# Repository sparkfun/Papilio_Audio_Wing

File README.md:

Papilio Audio Wing
==================
[  
*Papilio Audio Wing (WIG-11568)*](https://www.sparkfun.com/products/11568)

This board allows you to quickly add 2 stereo channels to your Papilio FPGA board. 

Repository Contents
-------------------
* **/Hardware** - All Eagle design files (.brd, .sch)
* **/Production** - Test bed files and production panel files

License Information
-------------------
The hardware is released under [Creative Commons Share-alike 3.0](http://creativecommons.org/licenses/by-sa/3.0/).

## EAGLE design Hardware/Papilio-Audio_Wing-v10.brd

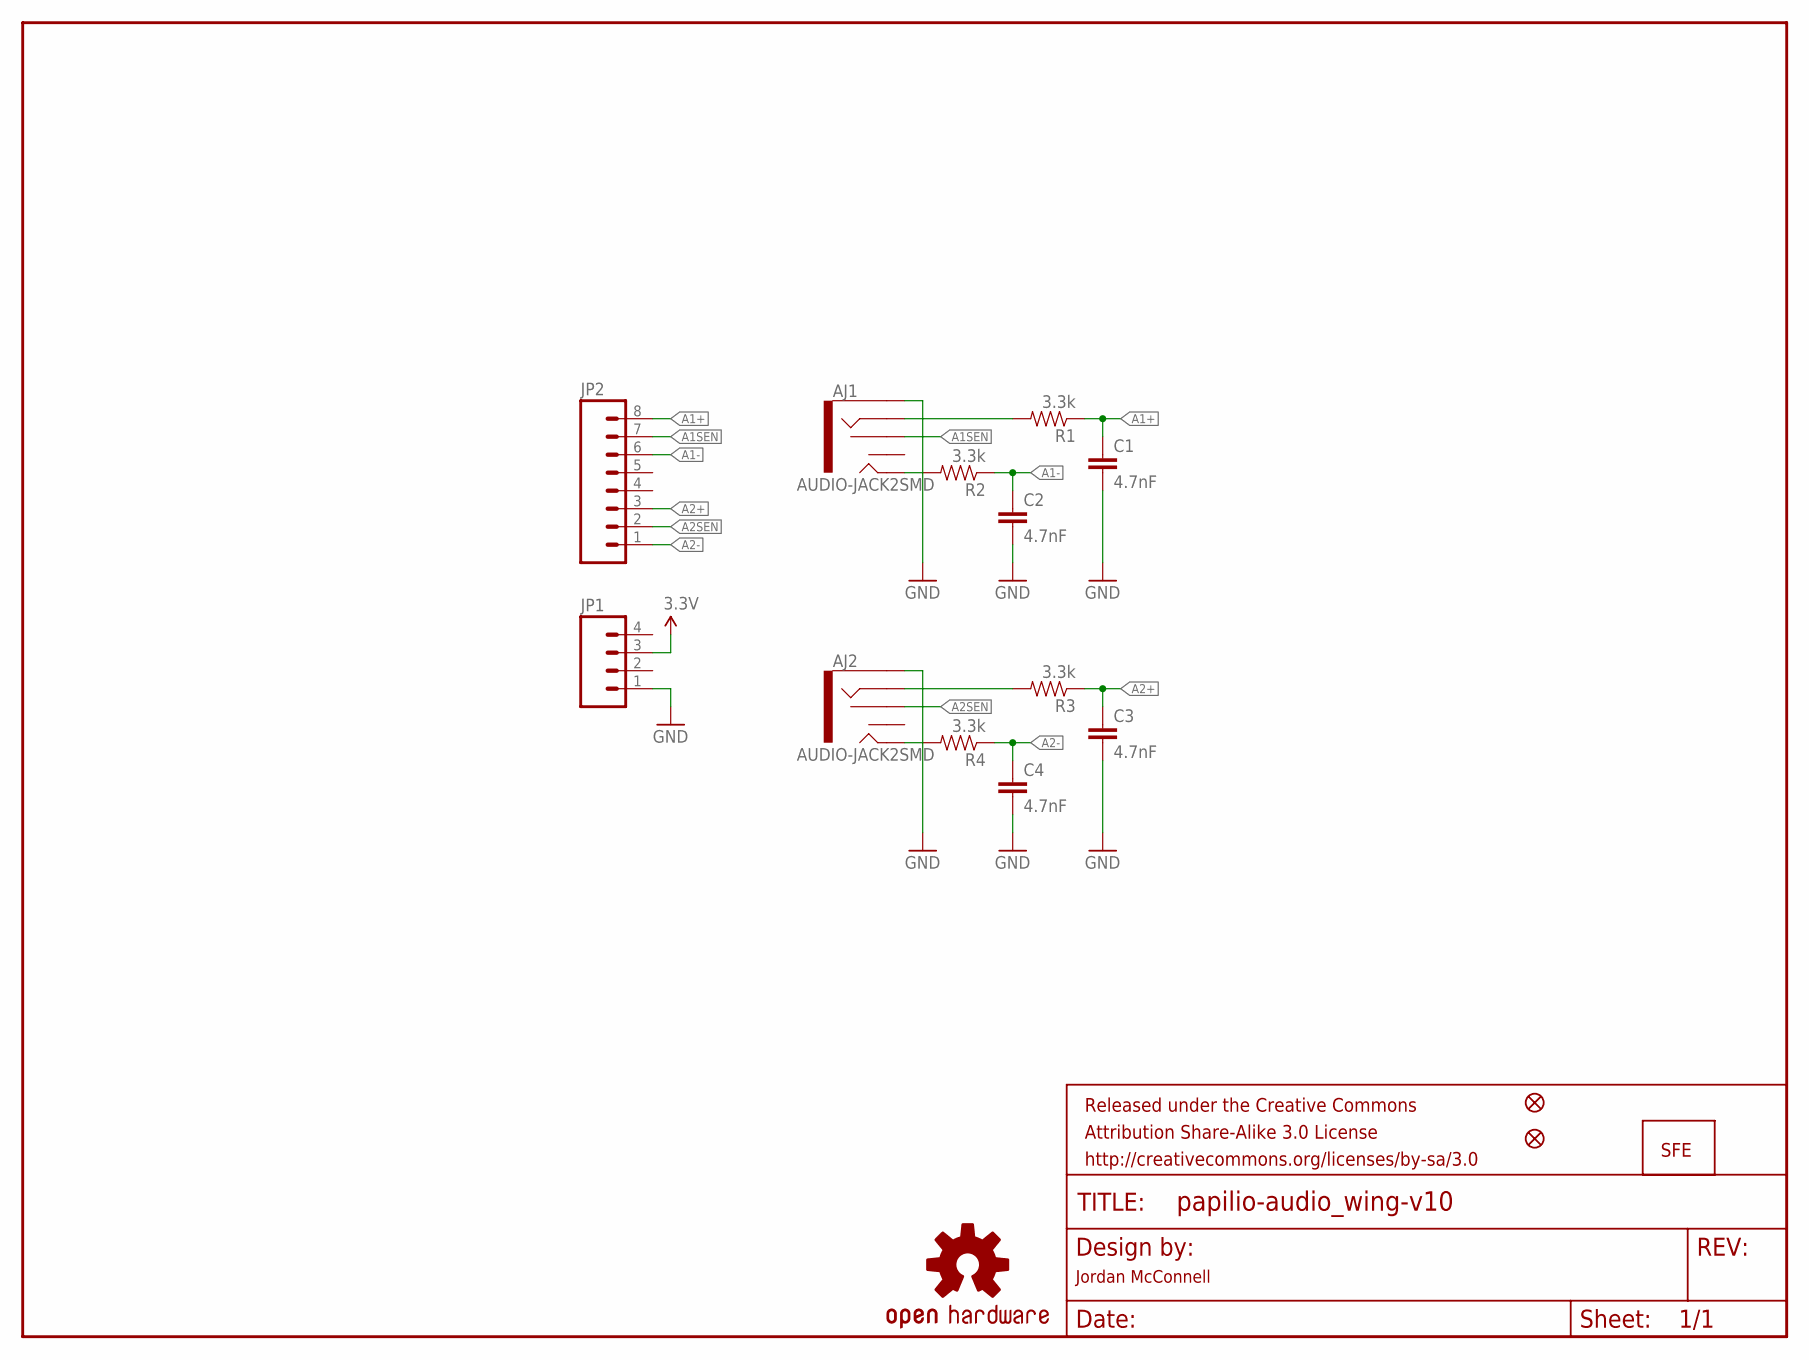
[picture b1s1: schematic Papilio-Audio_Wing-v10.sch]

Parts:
AJ1, AJ2: AUDIO-JACK2SMD; AUDIO-JACK-3.5MM-SMD
C1, C2, C3, C4: 4.7nF; 0402-CAP
FRAME2: FRAME-LETTER; CREATIVE_COMMONS
JP1: M04PTH; 1X04
JP2: M081X08; 1X08
JP4: LOGO-SFENEW; SFE-NEW-WEBLOGO
JP5, JP6: FIDUCIALUFIDUCIAL; MICRO-FIDUCIAL
R1, R2, R3, R4: 3.3k; 0402-RES
U$1: OSHW-LOGOS; OSHW-LOGO-S

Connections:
3.3V: JP1.3
A1+: C1.1, JP2.8, R1.1
A1-: C2.1, JP2.6, R2.1
A1SEN: AJ1.RSH, JP2.7
A2+: C3.1, JP2.3, R3.1
A2-: C4.1, JP2.1, R4.1
A2SEN: AJ2.RSH, JP2.2
GND: AJ1.SLEEVE, AJ2.SLEEVE, C1.2, C2.2, C3.2, C4.2, JP1.1
unnamed: AJ2.RING, R3.2
unnamed: AJ2.TIP, R4.2
unnamed: AJ1.RING, R1.2
unnamed: AJ1.TIP, R2.2

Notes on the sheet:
Jordan McConnell

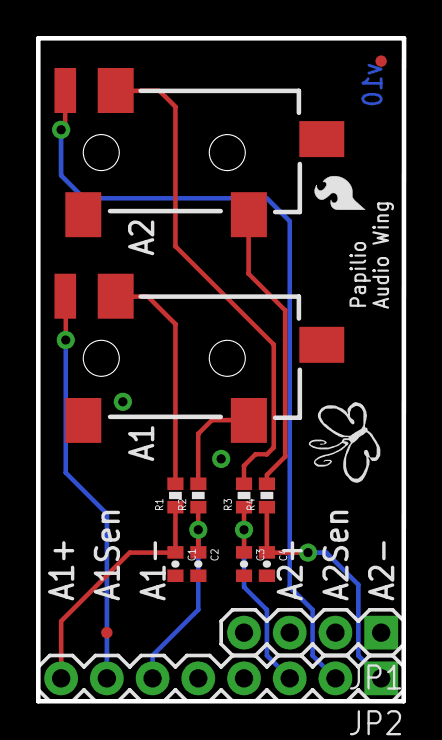
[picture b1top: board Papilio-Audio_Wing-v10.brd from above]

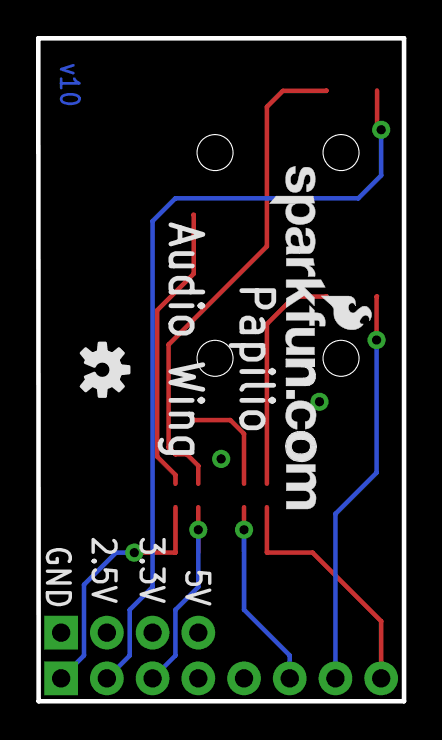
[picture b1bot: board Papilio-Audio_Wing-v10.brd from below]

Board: 2 copper layers, 20.3 x 36.8 mm, 19 parts (2 on the bottom side), 11 nets.

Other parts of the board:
FRAME1: FRAME-LETTER; CREATIVE_COMMONS
JP3: LOGO-SFESK; SFE-LOGO-FLAME

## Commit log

2013-08-19 Initial file commit
2013-08-19 Removing duplicate files

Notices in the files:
parts and their libraries:
SparkFun-Aesthetics: Licensing: CC v3.0 Share-Alike You are welcome to use this library for commercial purposes.
SparkFun-Aesthetics: Released under the Creative Commons Attribution Share-Alike 3.0 License
SparkFun-Aesthetics: Released under the Creative Commons
